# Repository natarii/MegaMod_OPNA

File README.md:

# OPNA MegaMod
This add-on board lets you play OPNA, OPN, and AY-3-8910 VGM files using your MegaGRRL Desktop.

**This board is provided as an experimental add-on. Software support is working, but incomplete. Software support may improve in the future.**

**MegaGRRL Desktop Firmware v0.97dev or newer is required!** See [Firmware Releases](https://git.agiri.ninja/natalie/megagrrl/-/releases)

# Usage
1. Power off the MegaGRRL Desktop.
2. Remove the YM2612 and SN76489, and seat the addon board into their sockets.
3. Set all 4 DIP switches on the desktop board to OFF.
4. Power on. The presence of the OPNA board will be detected upon boot. Play an OPNA/OPN/AY-3-8910 VGM file.

# Bill of Materials
| Ref.Dsg. | Value | Note |
| -------- | ----- | ---- |
| C1 | 10uF electrolytic |
| C2 | 2.7nF ceramic |
| C3 | 2.7nF ceramic |
| C4 | 68pF ceramic |
| C5 | 0.1uF ceramic |
| C6 | 0.1uF ceramic |
| C7 | 0.1uF ceramic |
| C8 | 0.1uF ceramic |
| C9 | 0.1uF ceramic |
| R1 | 33 ohm |
| R2 | 470 ohm |
| R3 | 1k ohm |
| RN1 | 10k bussed | Must be 9-pin bussed type |
| IC1 | YM2608 |
| IC2 | HM514260DJ | Tested with HM514260DJ. Other DRAMs may be compatible. Must be SOJ-40 footprint, 5V, 4Mbit (256Kx16), "fast page" type |
| IC3 | 74HC04 |
| IC4 | TL072 or SA5532 | Many opamps will work |
| IC5 | YM3016 |
| D1 | 1N5819 |
| Misc | 40 pins 0.1" machine pin header | 0.1" machine pin male-to-male headers, 40 pins total required. Must be machine pin type!!! |

All parts other than the DRAM at IC2 are THT.

# Assembly
1. Solder on the DRAM. Be careful to not short any pins underneath the IC
2. Solder on the remaining THT components. Pay attention that RN1 pin 1 goes towards the top of the board.
3. Solder on the pin headers (use MegaGRRL Desktop IC sockets for alignment)

# Gerber files
Gerbers for JLCPCB are in the `gerbers/` directory.

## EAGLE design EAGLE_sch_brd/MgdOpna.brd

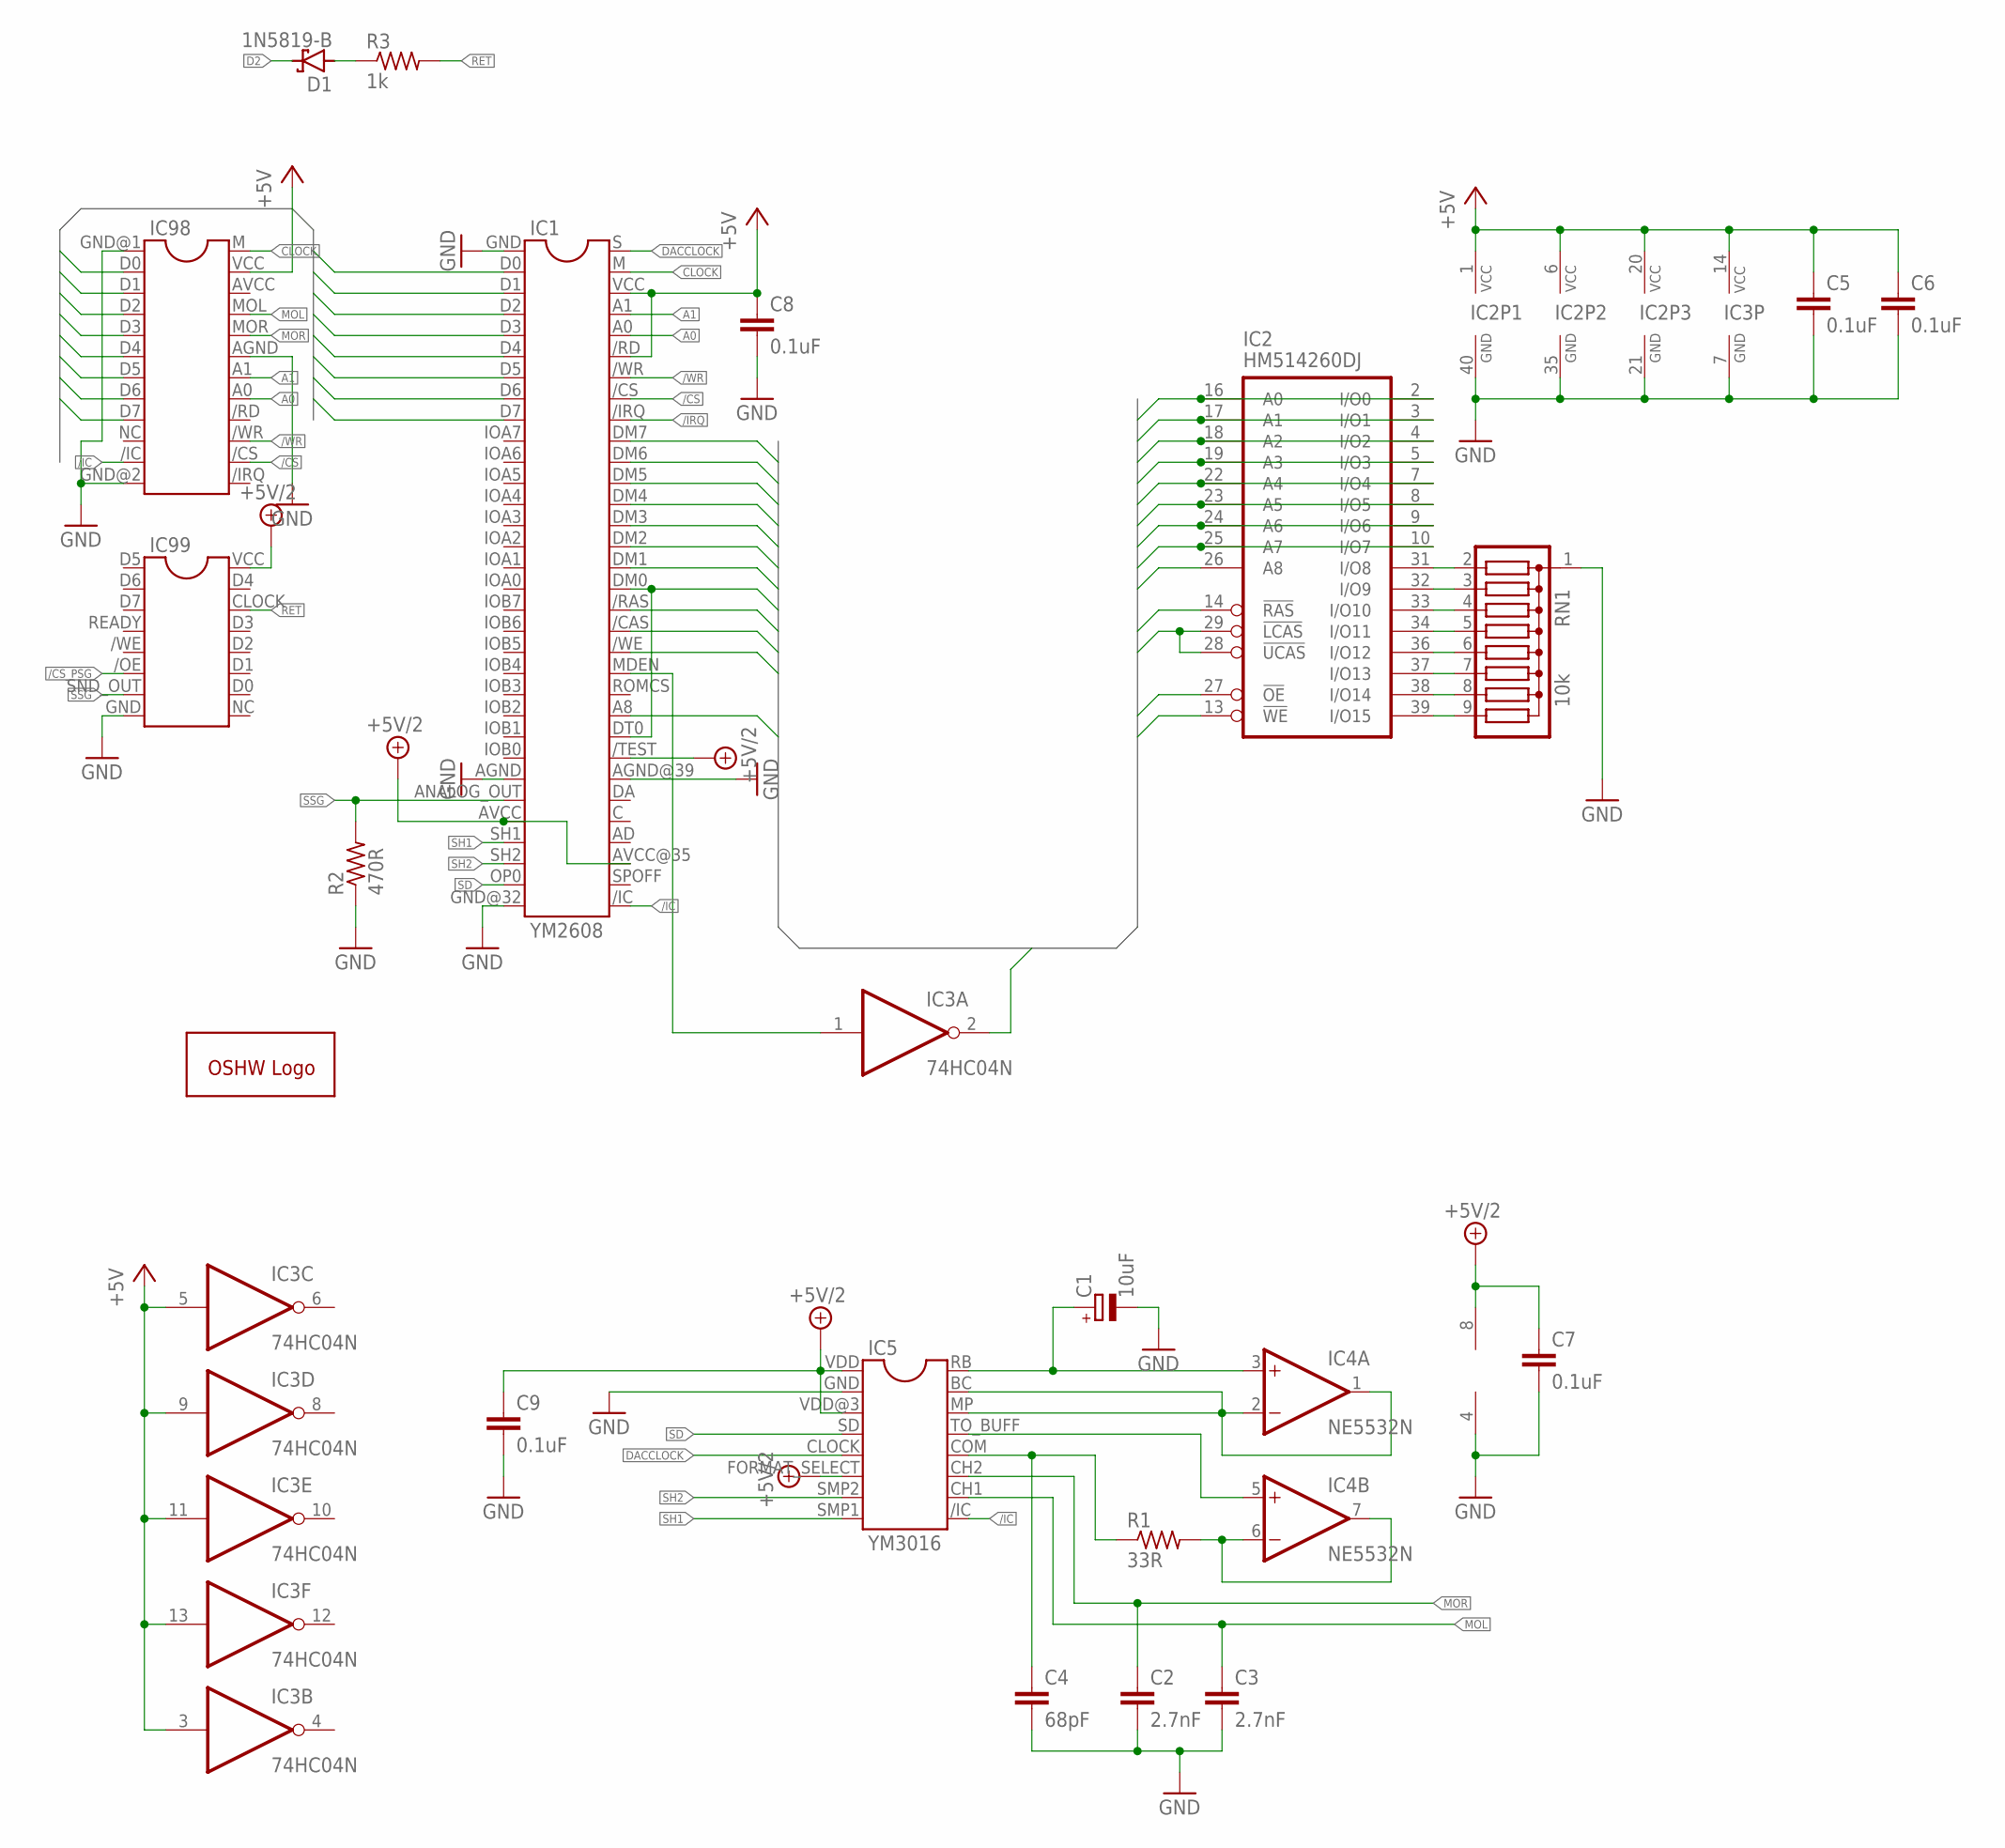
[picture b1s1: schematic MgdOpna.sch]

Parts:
C1: 10uF; E2,5-5
C2, C3: 2.7nF; C025-024X044
C4: 68pF; C025-024X044
C5, C6, C7, C8, C9: 0.1uF; C025-024X044
D1: 1N5819-B; DO41-7.6
GOLD_ORB_SM1: OSHWLOGOLOGO8MM; OSHW_8MM
IC1: YM2608
IC2: HM514260DJ; SOJ40-4
IC3: 74HC04N; DIL14
IC4: NE5532N; DIL08
IC5: YM3016
IC98: YM2612YM2612_NOSILK; YM2612_NOSILK
IC99: SN76489SN76489_NOSILK; SN76489_NOSILK
R1: 33R; 0204/7
R2: 470R; 0204/7
R3: 1k; 0204/7
RN1: 10k; SIL9

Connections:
+5V: C5.1, C6.1, C8.1, IC1./RD, IC1.VCC, IC2.1 (VCC), IC2.6 (VCC), IC2.20 (VCC), IC3.3 (I), IC3.5 (I), IC3.9 (I), IC3.11 (I), IC3.13 (I), IC3.14 (VCC), IC98.VCC
+5V/2: C7.1, C9.1, IC1./TEST, IC1.AVCC, IC1.AVCC@35 (AVCC), IC4.8 (V+), IC5.FORMAT_SELECT (6), IC5.VDD (1), IC5.VDD@3 (3), IC99.VCC
/CAS: IC1./CAS, IC2.28 (!UCAS), IC2.29 (!LCAS)
/CS: IC1./CS, IC98./CS
/CS_PSG: IC99./OE
/IC: IC1./IC, IC5./IC (9), IC98./IC
/IRQ: IC1./IRQ
/OE: IC2.27 (!OE), IC3.2 (O)
/RAS: IC1./RAS, IC2.14 (!RAS)
/WE: IC1./WE, IC2.13 (!WE)
/WR: IC1./WR, IC98./WR
A0: IC1.A0, IC98.A0
A1: IC1.A1, IC98.A1
A8: IC1.A8, IC2.26 (A8)
CLOCK: IC1.M, IC98.M
D0: IC1.D0, IC98.D0
D1: IC1.D1, IC98.D1
D2: D1.C, IC1.D2, IC98.D2
D3: IC1.D3, IC98.D3
D4: IC1.D4, IC98.D4
D5: IC1.D5, IC98.D5
D6: IC1.D6, IC98.D6
D7: IC1.D7, IC98.D7
DACCLOCK: IC1.S, IC5.CLOCK (5)
DM0: IC1.DM0, IC1.DT0 (DTO), IC2.2 (I/O0), IC2.16 (A0)
DM1: IC1.DM1, IC2.3 (I/O1), IC2.17 (A1)
DM2: IC1.DM2, IC2.4 (I/O2), IC2.18 (A2)
DM3: IC1.DM3, IC2.5 (I/O3), IC2.19 (A3)
DM4: IC1.DM4, IC2.7 (I/O4), IC2.22 (A4)
DM5: IC1.DM5, IC2.8 (I/O5), IC2.23 (A5)
DM6: IC1.DM6, IC2.9 (I/O6), IC2.24 (A6)
DM7: IC1.DM7, IC2.10 (I/O7), IC2.25 (A7)
GND: C1.-, C2.2, C3.2, C4.2, C5.2, C6.2, C7.2, C8.2, C9.2, IC1.AGND, IC1.AGND@39 (AGND), IC1.GND, IC1.GND@32 (GND), IC2.21 (GND), IC2.35 (GND), IC2.40 (GND), IC3.7 (GND), IC4.4 (V-), IC5.GND (2), IC98.AGND, IC98.GND@1 (GND), IC98.GND@2 (GND), IC99.GND, R2.1, RN1.1
MOL: C3.1, IC5.CH1 (10), IC98.MOL
MOR: C2.1, IC5.CH2 (11), IC98.MOR
unnamed: IC2.31 (I/O8), RN1.2
unnamed: IC2.32 (I/O9), RN1.3
unnamed: IC2.33 (I/O10), RN1.4
unnamed: IC2.34 (I/O11), RN1.5
unnamed: IC2.36 (I/O12), RN1.6
unnamed: IC2.37 (I/O13), RN1.7
unnamed: IC2.38 (I/O14), RN1.8
unnamed: IC2.39 (I/O15), RN1.9
unnamed: D1.A, R3.1
unnamed: IC1.MDEN, IC3.1 (I)
unnamed: C1.+, IC4.3 (+IN), IC5.RB (16)
unnamed: IC4.1 (OUT), IC4.2 (-IN), IC5.BC (15), IC5.MP (14)
unnamed: IC4.5 (+IN), IC5.TO_BUFF (13)
unnamed: IC4.6 (-IN), IC4.7 (OUT), R1.2
unnamed: C4.1, IC5.COM (12), R1.1
RET: IC99.CLOCK, R3.2
SD: IC1.OP0, IC5.SD (4)
SH1: IC1.SH1, IC5.SMP1 (8)
SH2: IC1.SH2, IC5.SMP2 (7)
SSG: IC1.ANALOG_OUT, IC99.SND_OUT, R2.2

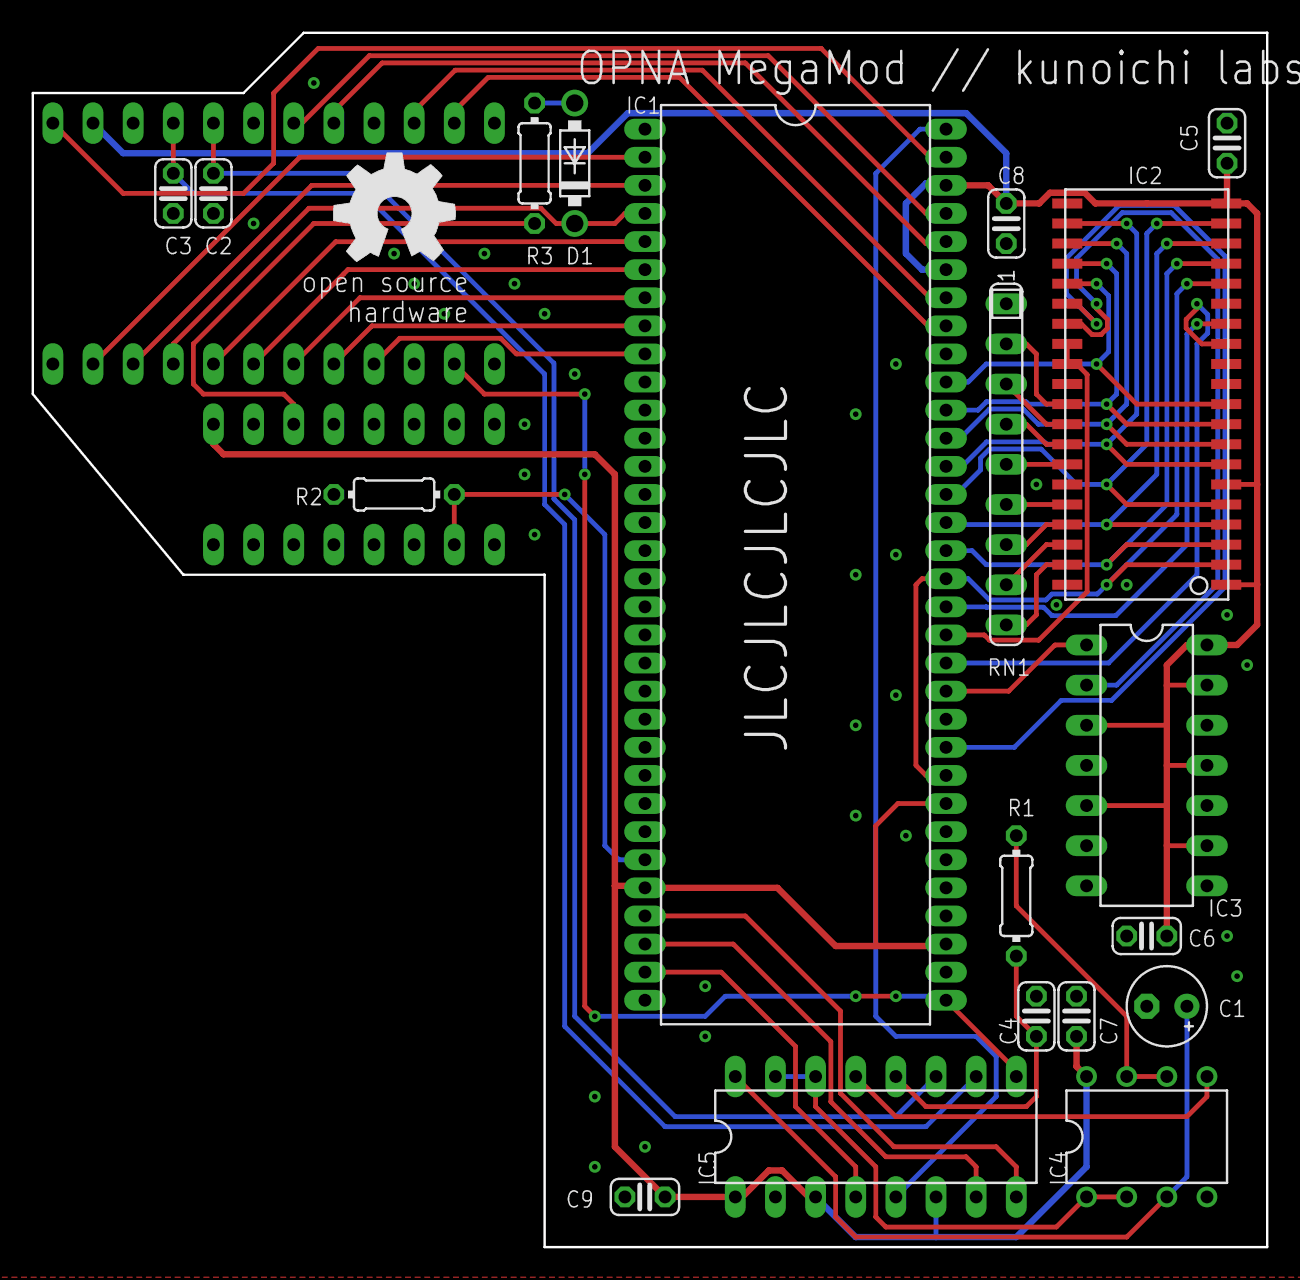
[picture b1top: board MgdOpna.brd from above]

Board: 2 copper layers, 78.1 x 76.8 mm, 22 parts (0 on the bottom side), 53 nets.

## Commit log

2020-11-03 Add note about RN1 to readme
